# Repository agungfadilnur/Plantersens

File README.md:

# Lora RF95 Shield Arduino
Prototype Lora RF95 Shield on Arduino Uno for PlanterSens

## Testing PCB v1.0
I make a prototype shield RF95 by cheap production 😁

For more information about project at  [Lora RF95 Shield](https://agungfadilnur.github.io)

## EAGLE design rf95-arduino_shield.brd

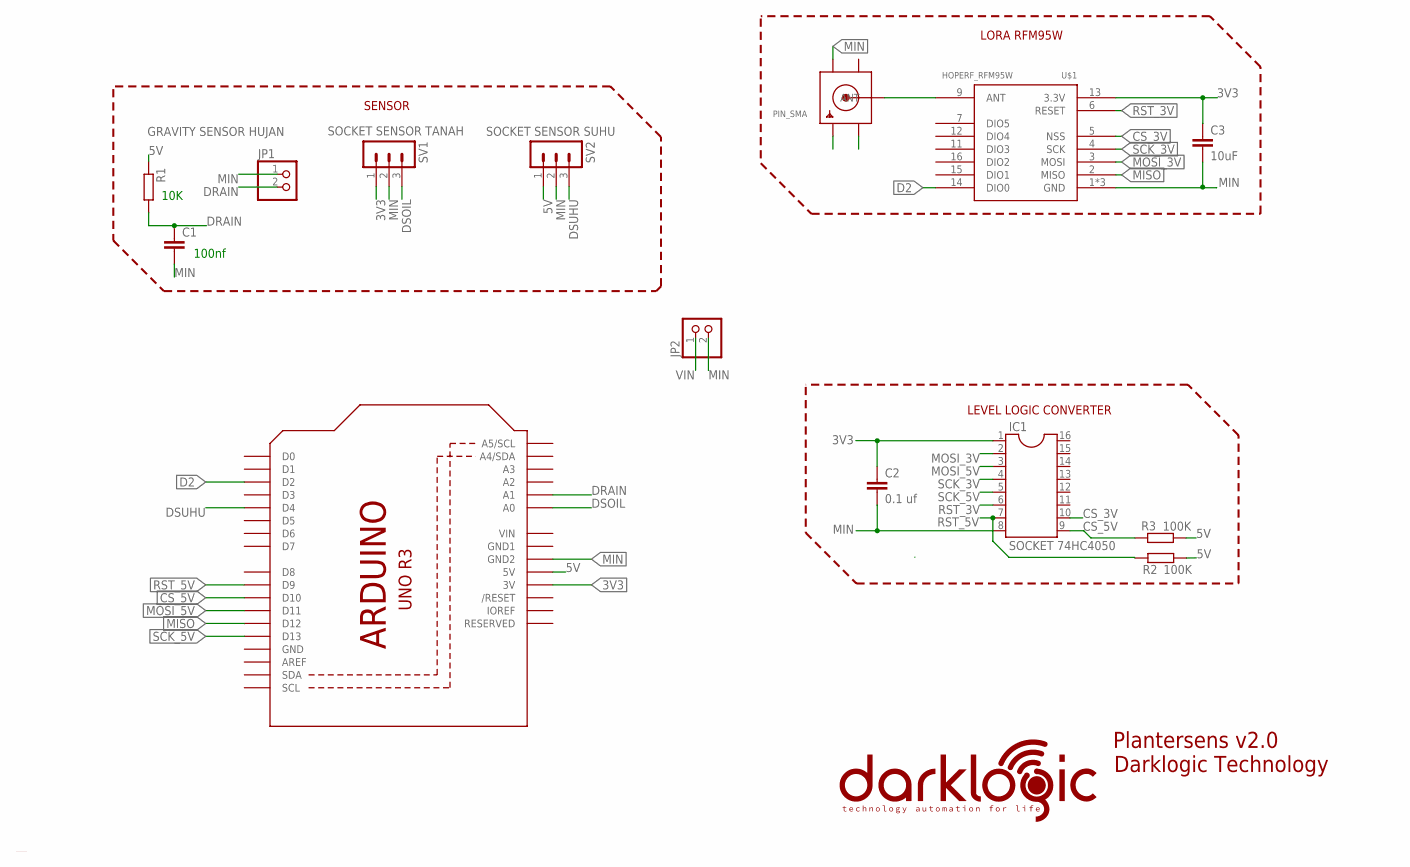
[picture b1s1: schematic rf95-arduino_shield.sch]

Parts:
C1: C2.5/2; C2.5-2
C2: 0.1 uf; C025-024X044
C3: 10uF; C025-024X044
IC1: SOCKET 74HC4050; SOCKET-16
JP1: GRAVITY SENSOR HUJAN; 1X02
JP2: PINHD-1X2; 1X02
PIN_SMA: SMACONNECTOR_EDGE; SMA_EDGELAUNCH
R1: R-EU_0204/7; 0204/7
R2, R3: 100K; 0204/7
SV1: SOCKET SENSOR TANAH; MA03-1
SV2: SOCKET SENSOR SUHU; MA03-1
U1: ARDUINOR3-BPLACE
U$1: HOPERF_RFM95W

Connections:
3V3: C2.1, C3.1, IC1.1, SV1.1, U1.3V, U$1.13 (3.3V)
5V: R1.1, R2.1, R3.2, SV2.1, U1.5V
ANT: PIN_SMA.P (ANT), U$1.9 (ANT)
CS_3V: IC1.10, U$1.5 (NSS)
CS_5V: IC1.9, R3.1, U1.D10
D2: U1.D2, U$1.14 (DIO0)
DRAIN: C1.1, JP1.2, R1.2, U1.A1
DSOIL: SV1.3, U1.A0
DSUHU: SV2.3, U1.D4
GND1: U1.GND1
GND3: PIN_SMA.GND@2 (GND3)
MIN: C1.2, C2.2, C3.2, IC1.8, JP1.1, JP2.2, PIN_SMA.GND@1 (GND4), SV1.2, SV2.2, U1.GND, U1.GND2, U$1.1 (GND), U$1.8 (GND), U$1.10 (GND)
MISO: U1.D12, U$1.2 (MISO)
MOSI_3V: IC1.2, U$1.3 (MOSI)
MOSI_5V: IC1.3, U1.D11
RST_3V: IC1.6, U$1.6 (RESET)
RST_5V: IC1.7, R2.2, U1.D9
SCK_3V: IC1.4, U$1.4 (SCK)
SCK_5V: IC1.5, U1.D13
VIN: JP2.1, U1.VIN

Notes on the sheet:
10K
100nf
LEVEL LOGIC CONVERTER
LORA RFM95W
SENSOR
Plantersens v2.0
Darklogic Technology
C:/Users/a/Documents/Dark Logic/Project/LORA/darklogic hitam copy.bmp

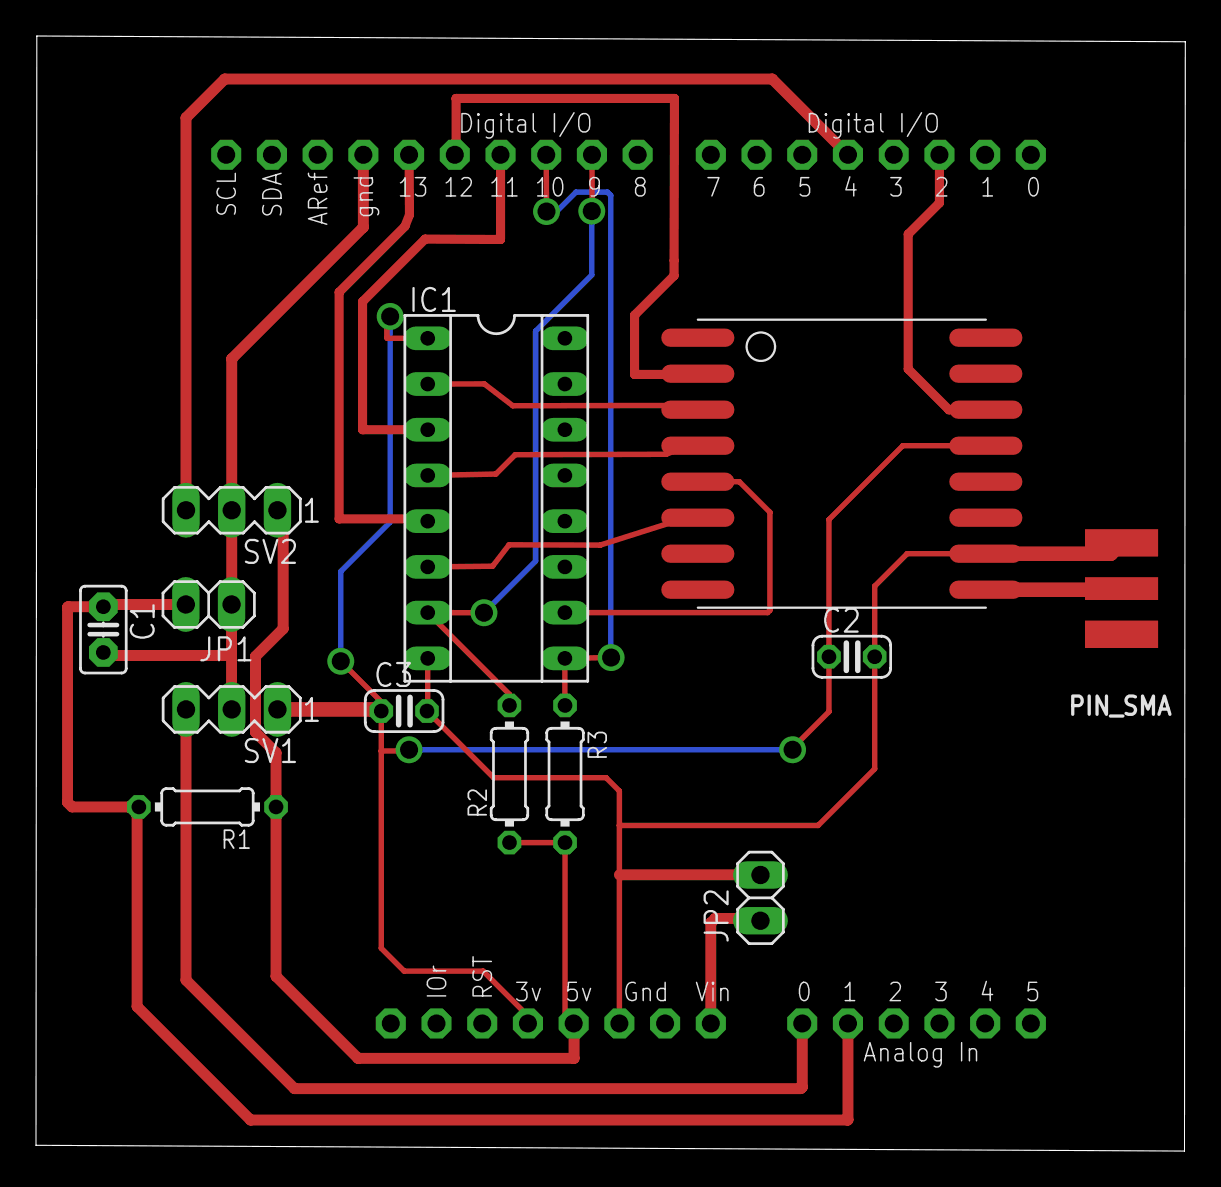
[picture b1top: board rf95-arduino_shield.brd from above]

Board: 2 copper layers, 63.9 x 61.9 mm, 14 parts (0 on the bottom side), 18 nets.
